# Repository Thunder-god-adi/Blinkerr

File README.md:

# 555-Led-chaser
I made this bcs i want too

**FINAL RENDER**

**PCB**
\

**SCHEMATICS**

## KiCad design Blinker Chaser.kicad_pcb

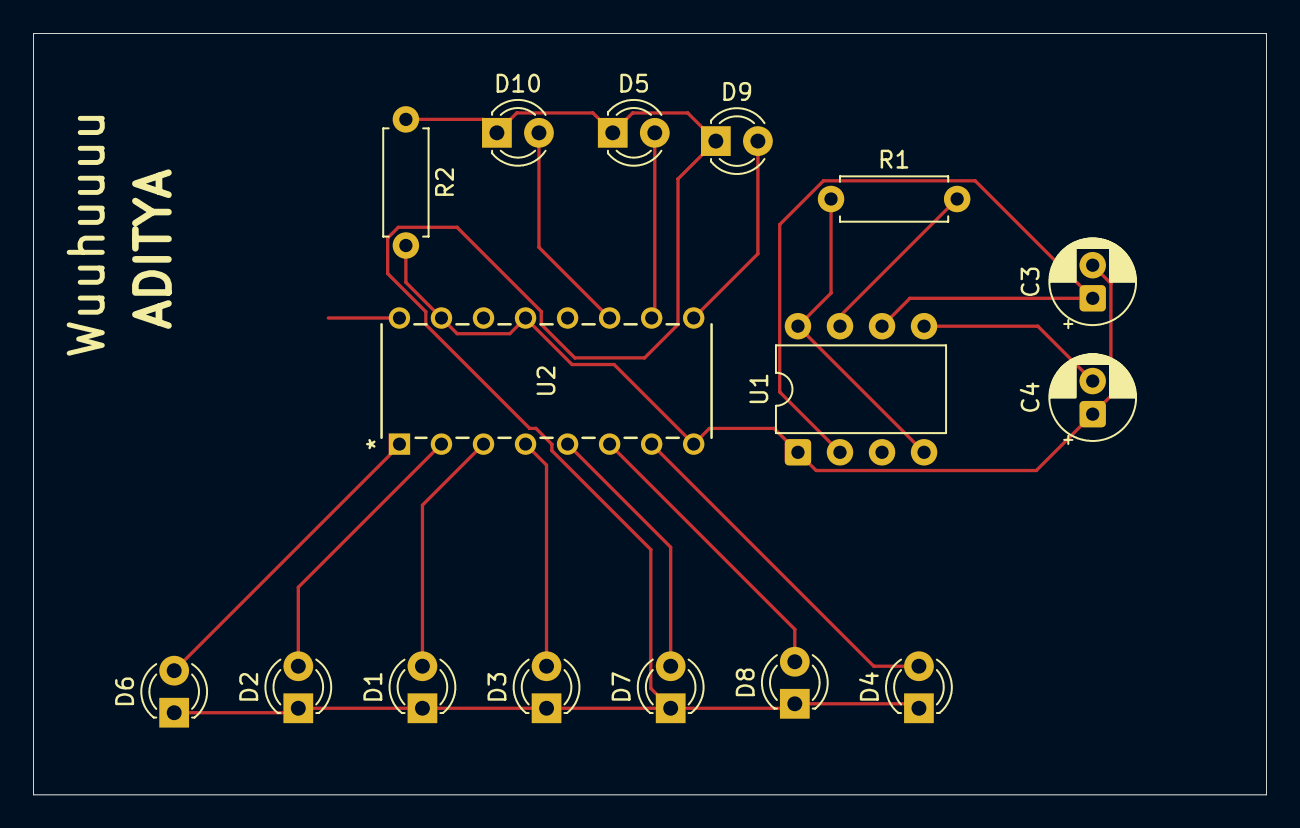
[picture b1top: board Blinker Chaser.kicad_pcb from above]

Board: 2 copper layers, 74.5 x 46.0 mm, 16 parts (0 on the bottom side), 17 nets.

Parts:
C3: 1uF; CP_Radial_D5.0mm_P2.00mm
C4: 0.01uF; CP_Radial_D5.0mm_P2.00mm
D1, D2, D3, D4, D5, D6, D7, D8, D9, D10: LED; LED_D3.0mm
R1: 1K; R_Axial_DIN0207_L6.3mm_D2.5mm_P7.62mm_Horizontal
R2: 470; R_Axial_DIN0207_L6.3mm_D2.5mm_P7.62mm_Horizontal
U1: NE555P; DIP-8_W7.62mm
U2: 4017; N16

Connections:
+5V: R1.1, U1.4 (R), U1.8 (VCC), U2.16 (VDD)
GND: C3.2, C4.1, R2.2, U1.1 (GND), U2.8 (VSS), U2.13 (CKEN), U2.15 (Reset)
unnamed: D1.2 (A), U2.3 (Q0)
unnamed: D1.1 (K), D2.1 (K), D3.1 (K), D4.1 (K), D5.1 (K), D6.1 (K), D7.1 (K), D8.1 (K), D9.1 (K), D10.1 (K), R2.1
unnamed: D2.2 (A), U2.2 (Q1)
unnamed: D3.2 (A), U2.4 (Q2)
unnamed: D4.2 (A), U2.7 (Q3)
unnamed: D5.2 (A), U2.10 (Q4)
unnamed: D6.2 (A), U2.1 (Q5)
unnamed: D7.2 (A), U2.5 (Q6)
unnamed: D8.2 (A), U2.6 (Q7)
unnamed: D9.2 (A), U2.9 (Q8)
unnamed: D10.2 (A), U2.11 (Q9)
unnamed: C4.2, U1.5 (CV)
unnamed: R1.2, U1.7 (DIS)
OUT: U1.3 (Q), U2.14 (CLK)
TR: C3.1, U1.2 (TR), U1.6 (THR)
